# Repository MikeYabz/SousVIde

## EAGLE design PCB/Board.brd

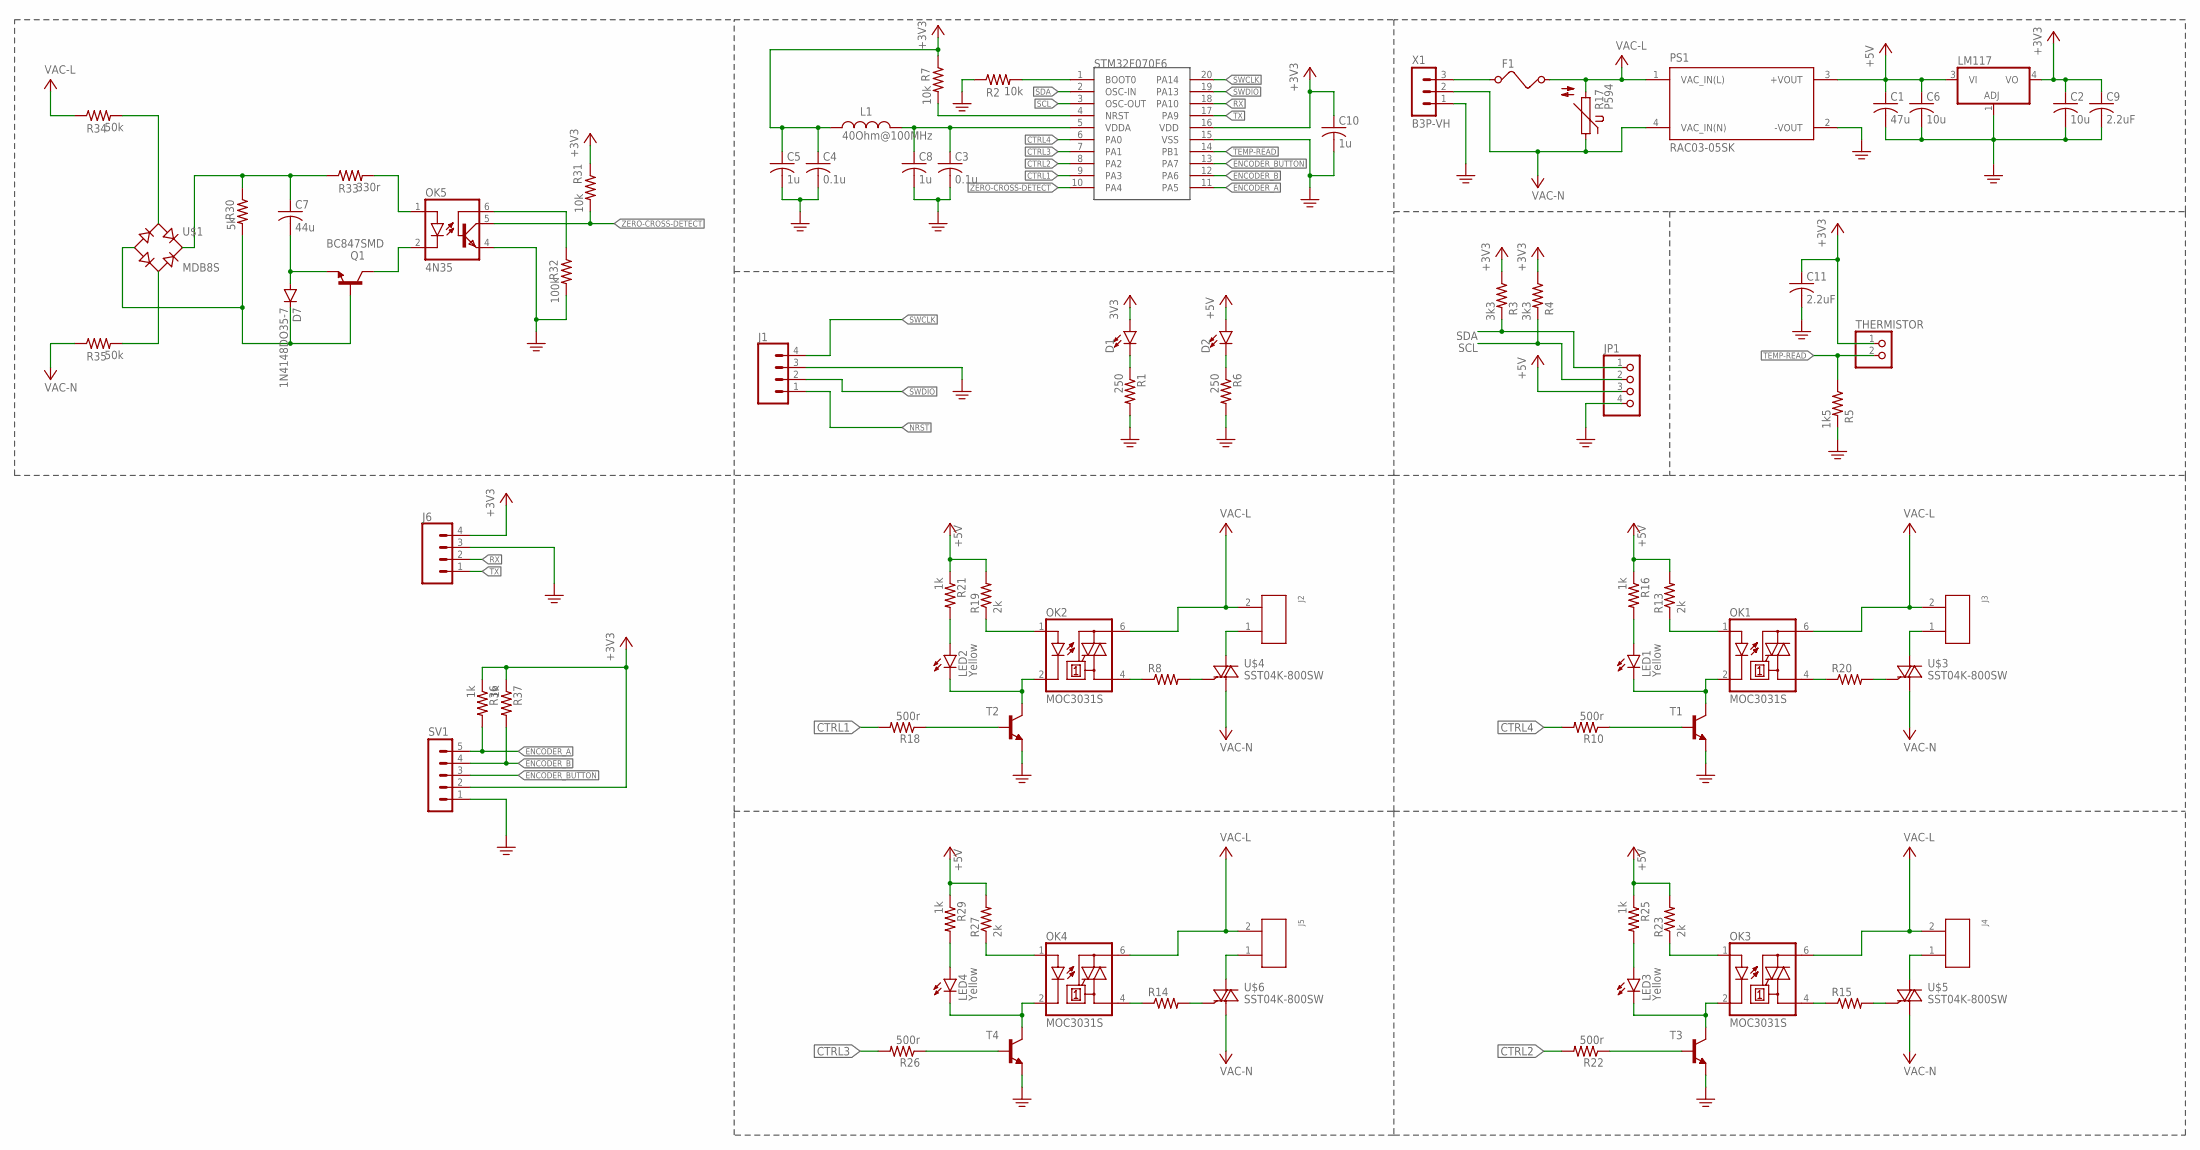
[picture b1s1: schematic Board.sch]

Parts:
C1: 47u; C0603
C2, C6: 10u; C0603
C3, C4: 0.1u; C0603
C5, C8, C10: 1u; C0603
C7: 44u; C0603
C9, C11: 2.2uF; C0603
D1, D2: LED0603; LED-0603
D7: 1N4148DO35-7; DO35-7
F1: FUSE
J1, J6: CONN_04; 1X04
J2, J3, J4, J5: 66100211622
JP1: PINHD-1X4; 1X04
L1: 40Ohm@100MHz; WE-CBF_0805(W=3.0)
LED1, LED2, LED3, LED4: Yellow; LED-0603
LM117: 317EMP; SOT223
OK1, OK2, OK3, OK4: MOC3031S; DIL6-SMD
OK5: 4N35; DIL06
PS1: RAC03-05SK; CONV_RAC03-05SK
Q1: BC847SMD; SOT23
R1, R6: 250; R0603
R2, R7, R31: 10k; R0603
R3, R4: 3k3; R0603
R5: 1k5; R0603
R8, R14, R15, R20: R-US_0613/15; P0613/15
R10, R18, R22, R26: 500r; R0603
R13, R19, R23, R27: 2k; R0603
R16, R21, R25, R29, R36, R37: 1k; R0603
R17: P594
R30: 5k; R0603
R32: 100k; R0603
R33: 330r; R0603
R34, R35: 50k; R0603
STM32F070F6: STM32F07; TSSOP20
SV1: MA05-1
T1, T2, T3, T4: -NPN-SOT23-EBC; SOT23-EBC
THERMISTOR: PINHD-1X2; 1X02
U$1: MDB8S; 4-MICRODIP
U$3, U$4, U$5, U$6: SST04K-800SW; DPAK
X1: B3P-VH

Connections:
+3V3: C2.1, C4.1, C5.1, C9.1, C10.1, C11.1, D1.A, J6.4, L1.1, LM117.4 (VO), R3.1, R4.1, R7.1, R31.1, R36.1, R37.1, STM32F070F6.16 (VDD), SV1.2, THERMISTOR.1
+5V: C1.1, C6.1, D2.A, JP1.3, LM117.3 (VI), PS1.3 (+VOUT), R13.2, R16.1, R19.2, R21.1, R23.2, R25.1, R27.2, R29.1
CTRL1: R18.2, STM32F070F6.9 (PA3)
CTRL2: R22.2, STM32F070F6.8 (PA2)
CTRL3: R26.2, STM32F070F6.7 (PA1)
CTRL4: R10.2, STM32F070F6.6 (PA0)
ENCODER_A: R36.2, STM32F070F6.11 (PA5), SV1.5
ENCODER_B: R37.2, STM32F070F6.12 (PA6), SV1.4
ENCODER_BUTTON: STM32F070F6.13 (PA7), SV1.3
FET1: R18.1, T2.B
FET2: R22.1, T3.B
FET3: R10.1, T1.B
FET4: R26.1, T4.B
unnamed: D1.C, R1.1
unnamed: D2.C, R6.1
unnamed: C3.1, C8.1, L1.2, STM32F070F6.5 (VDDA)
unnamed: LED2.C, OK2.2 (C), T2.C
unnamed: LED1.C, OK1.2 (C), T1.C
unnamed: OK1.4 (A1), R20.1
unnamed: OK1.1 (A), R13.1
unnamed: R20.2, U$3.3 (G)
unnamed: LED1.A, R16.2
unnamed: J3.1, U$3.4 (A2)
unnamed: OK2.1 (A), R19.1
unnamed: OK2.4 (A1), R8.1
unnamed: R8.2, U$4.3 (G)
unnamed: LED2.A, R21.2
unnamed: J2.1, U$4.4 (A2)
unnamed: LED3.C, OK3.2 (C), T3.C
unnamed: OK3.1 (A), R23.1
unnamed: OK3.4 (A1), R15.1
unnamed: R15.2, U$5.3 (G)
unnamed: LED3.A, R25.2
unnamed: J4.1, U$5.4 (A2)
unnamed: LED4.C, OK4.2 (C), T4.C
unnamed: OK4.1 (A), R27.1
unnamed: OK4.4 (A1), R14.1
unnamed: R14.2, U$6.3 (G)
unnamed: LED4.A, R29.2
unnamed: J5.1, U$6.4 (A2)
unnamed: D7.C, Q1.1 (B), R30.2, U$1.4 (-)
unnamed: C7.1, R30.1, R33.1, U$1.3 (+)
unnamed: C7.2, D7.A, Q1.2 (E)
unnamed: OK5.2 (C), Q1.3 (C)
unnamed: OK5.6 (BAS), R32.1
unnamed: OK5.1 (A), R33.2
unnamed: R34.2, U$1.1 (AC1)
unnamed: R35.2, U$1.2 (AC2)
unnamed: R2.2, STM32F070F6.1 (BOOT0)
NRST: J1.1, R7.2, STM32F070F6.4 (NRST)
PE: C1.2, C2.2, C3.2, C4.2, C5.2, C6.2, C8.2, C9.2, C10.2, C11.2, J1.3, J6.3, JP1.4, LM117.1 (ADJ), OK5.4 (EMI), PS1.2 (-VOUT), R1.2, R2.1, R5.2, R6.2, R32.2, STM32F070F6.15 (VSS), SV1.1, T1.E, T2.E, T3.E, T4.E, X1.1
RX: J6.2, STM32F070F6.18 (PA10)
SCL: JP1.2, R4.2, STM32F070F6.3 (OSC-OUT)
SDA: JP1.1, R3.2, STM32F070F6.2 (OSC-IN)
SWCLK: J1.4, STM32F070F6.20 (PA14)
SWDIO: J1.2, STM32F070F6.19 (PA13)
TEMP-READ: R5.1, STM32F070F6.14 (PB1), THERMISTOR.2
TX: J6.1, STM32F070F6.17 (PA9)
V+: F1.2, J2.2, J3.2, J4.2, J5.2, OK1.6 (A2), OK2.6 (A2), OK3.6 (A2), OK4.6 (A2), PS1.1 (VAC_IN(L)), R17.2, R34.1
V-: PS1.4 (VAC_IN(N)), R17.1, R35.1, U$3.1 (A1), U$4.1 (A1), U$5.1 (A1), U$6.1 (A1), X1.2
VAC(L)-INPUT: F1.1, X1.3
ZERO-CROSS-DETECT: OK5.5 (COL), R31.2, STM32F070F6.10 (PA4)

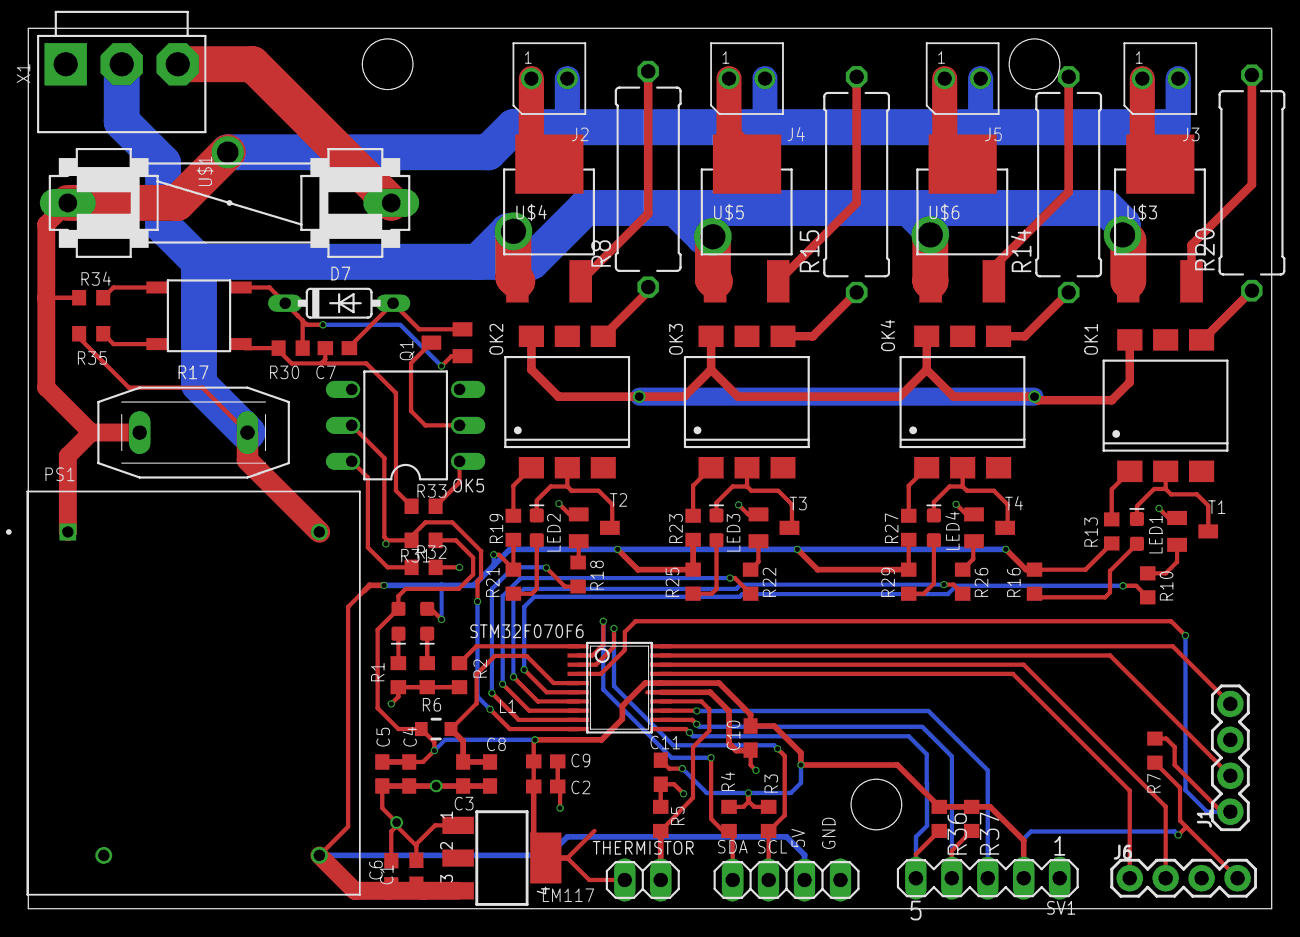
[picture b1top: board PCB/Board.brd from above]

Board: 2 copper layers, 87.9 x 62.2 mm, 80 parts (0 on the bottom side), 62 nets.

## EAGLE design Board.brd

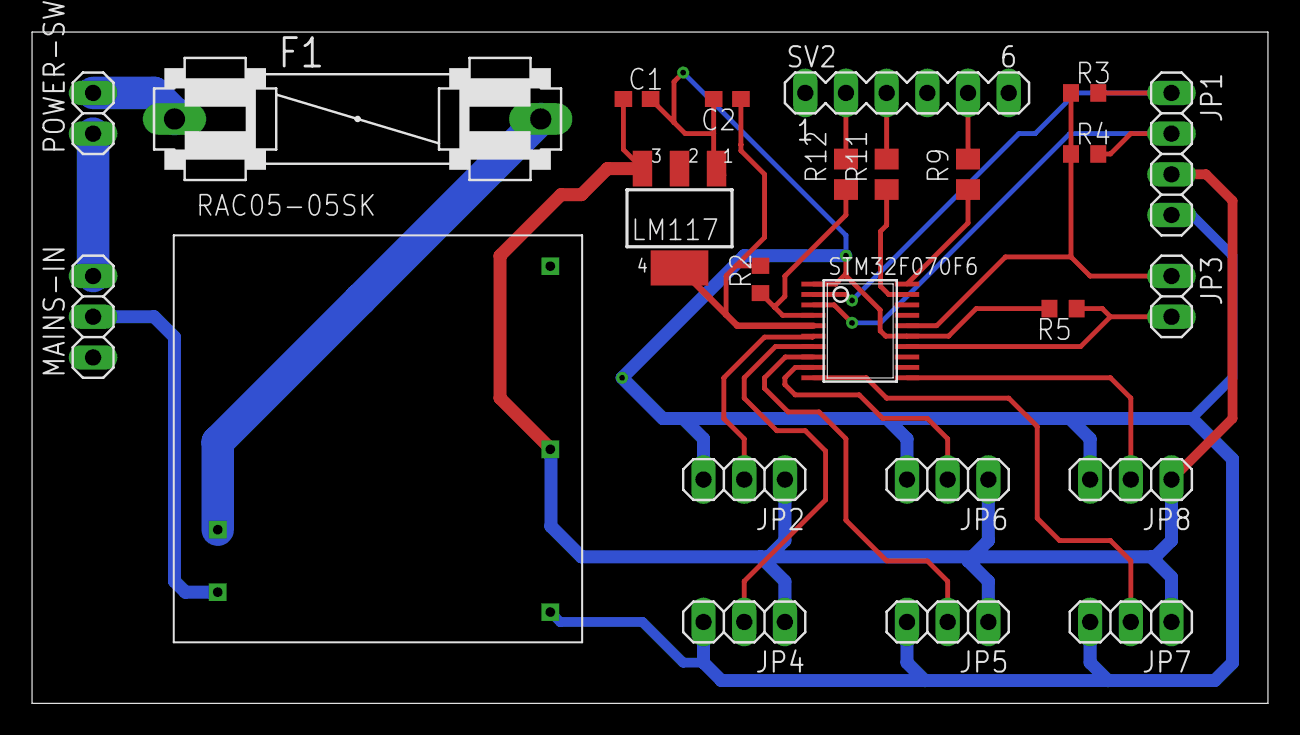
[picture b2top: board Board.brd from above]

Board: 2 copper layers, 77.1 x 41.9 mm, 24 parts (0 on the bottom side), 22 nets.

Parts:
C1: 47u; C0603
C2: 10u; C0603
F1: FUSE
JP1: 1X04
JP2, JP4, JP5, JP6, JP7, JP8: 1X03
JP3: 1X02
LM117: 317EMP; SOT223
MAINS-IN: 1X03
POWER-SWITCH: 1X02
R2, R3, R4: 3k3; R0603
R5: 1k5; R0603
R9, R11, R12: 250; R0805
RAC05-05SK: AC/DC-CONVERTER
STM32F070F6: TSSOP20
SV2: MA06-1

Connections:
+3V3: C2.1, JP3.1, LM117.4, R2.2, R3.1, R4.1, STM32F070F6.5, STM32F070F6.16, SV2.6
+5V: C1.1, JP1.3, JP2.1, JP4.1, JP5.1, JP6.1, JP7.1, JP8.1, LM117.3, RAC05-05SK.P$4
unnamed: MAINS-IN.3, POWER-SWITCH.1
unnamed: R9.2, SV2.5
unnamed: R11.2, SV2.3
unnamed: R12.2, SV2.2
NRST: R2.1, R12.1, STM32F070F6.4
PE: C1.2, C2.2, JP1.4, JP2.3, JP4.3, JP5.3, JP6.3, JP7.3, JP8.3, LM117.1, R5.2, RAC05-05SK.P$5, STM32F070F6.1, STM32F070F6.15
RELAY1: JP2.2, STM32F070F6.6
RELAY2: JP4.2, STM32F070F6.7
RELAY3: JP5.2, STM32F070F6.8
RELAY4: JP6.2, STM32F070F6.9
RELAY5: JP7.2, STM32F070F6.10
RELAY6: JP8.2, STM32F070F6.11
SCL: JP1.2, R4.2, STM32F070F6.3
SDA: JP1.1, R3.2, STM32F070F6.2
SWCLK: R9.1, STM32F070F6.20
SWDIO: R11.1, STM32F070F6.19
TEMP-READ: JP3.2, R5.1, STM32F070F6.14
VAC(L): F1.2, RAC05-05SK.P$1
VAC(L)-INPUT: F1.1, POWER-SWITCH.2
VAC(N): MAINS-IN.2, RAC05-05SK.P$2

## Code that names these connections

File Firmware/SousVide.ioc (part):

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Mcu.Name=STM32F070F6Px
Mcu.Package=TSSOP20
Mcu.UserName=STM32F070F6Px
PA0.GPIOParameters=GPIO_Label
PA0.GPIO_Label=Relay1
PA0.Signal=GPIO_Output
PA1.GPIOParameters=GPIO_Label
PA1.GPIO_Label=Relay2
PA1.Signal=GPIO_Output
PA10.Mode=Asynchronous
PA10.Signal=USART1_RX
PA13.Mode=Serial_Wire
PA13.Signal=SYS_SWDIO
PA14.Mode=Serial_Wire
PA14.Signal=SYS_SWCLK
PA2.GPIOParameters=GPIO_Label
PA2.GPIO_Label=Relay3
PA2.Signal=GPIO_Output
PA3.GPIOParameters=GPIO_Label
PA3.GPIO_Label=Relay4
PA3.Signal=GPIO_Output
PA4.GPIOParameters=GPIO_Label
PA4.GPIO_Label=Relay5
PA4.Signal=GPIO_Output
PA5.GPIOParameters=GPIO_Label
PA5.GPIO_Label=Relay6
PA5.Signal=GPIO_Output
PA6.GPIOParameters=GPIO_PuPd
PA6.GPIO_PuPd=GPIO_PULLDOWN
PA6.Signal=GPIO_Input
PA7.GPIOParameters=GPIO_PuPd
PA7.GPIO_PuPd=GPIO_PULLDOWN
PA7.Signal=GPIO_Input
PA9.Mode=Asynchronous
PA9.Signal=USART1_TX
PB1.GPIOParameters=GPIO_Label
PB1.GPIO_Label=TempRead
PB1.Mode=IN9
PB1.Signal=ADC_IN9
PF0-OSC_IN.Mode=I2C
PF0-OSC_IN.Signal=I2C1_SDA
PF1-OSC_OUT.Mode=I2C
PF1-OSC_OUT.Signal=I2C1_SCL
board=SousVide

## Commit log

2018-05-10 Worked on Schematic
2018-05-16 preliminary board design
2018-05-16 deleted backups
2018-05-17 rev 1 sent to fab
2018-05-29 premilinary rev 2, fixed Ac/DC footprint, removed on-board switch and added mains outputs
2018-05-29 added DC power LEDs
2018-06-04 added lcd i2c support and thermistor calculations
2018-06-06 code for lcd time and temperature display added, missing thermistor calculations
2018-06-07 added thermistor reading and data filtering, POC ready
2018-06-07 code cleaned up and began state machine
2018-06-07 reoganized code, added button reading, state machine still not fully implemented
2018-06-08 state machine and UI implemeted but completely untested
2018-06-10 making a single board for everything
2018-10-13 updated temperature sensing algorithm to a more accurate algorithm
2018-10-25 added CAD
2018-10-29 updated cad
2019-09-10 updated CAD and made single PCB instead of seperate
2020-09-17 started v4 redesign

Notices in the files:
parts and their libraries:
SparkFun-LED: Licensing: Creative Commons ShareAlike 4.0 International - https://creativecommons.org/licenses/by-sa/4.0
Wurth_Elektronik_Electromechanic_Wire_to: Copyright: Würth Elektronik
